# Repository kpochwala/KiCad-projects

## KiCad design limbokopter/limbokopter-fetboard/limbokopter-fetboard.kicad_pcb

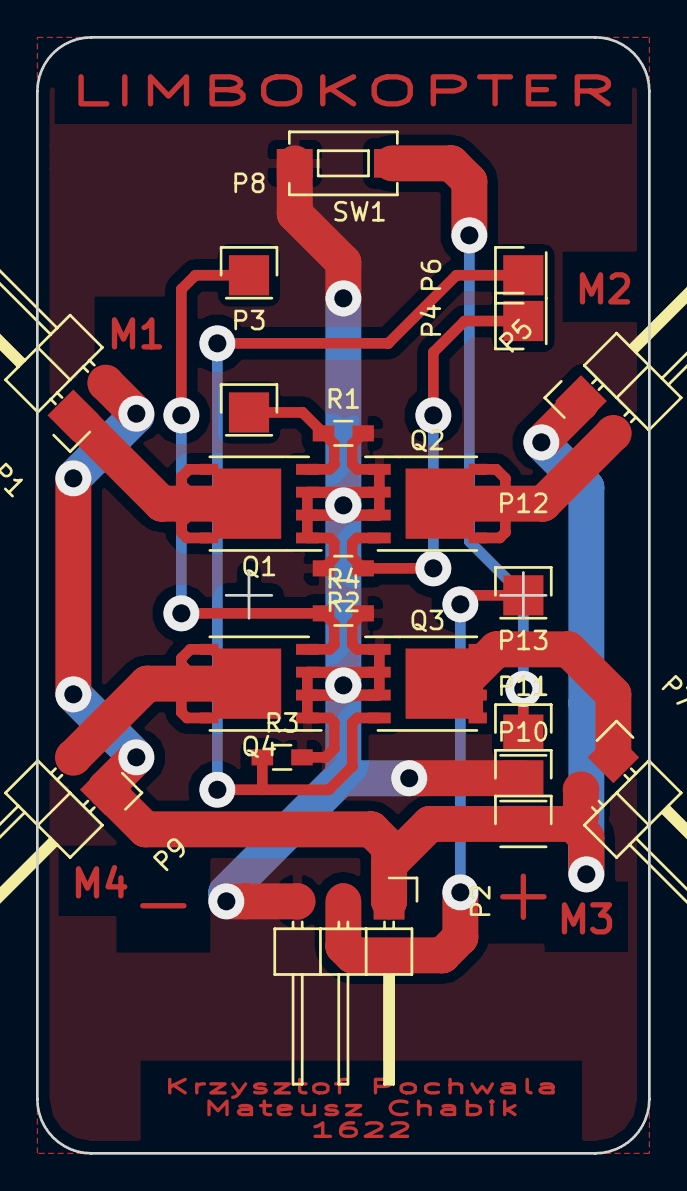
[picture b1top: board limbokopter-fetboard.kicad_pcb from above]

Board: 2 copper layers, 34.0 x 62.0 mm, 22 parts (0 on the bottom side), 12 nets.

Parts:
P1: M1; Pin_Header_Angled_1x02
P2: CONN_01X03; Pin_Header_Angled_1x03
P3: PWM1; Pin_Header_Straight_1x01
P4: PWM2; Pin_Header_Straight_1x01
P5: M2; Pin_Header_Angled_1x02
P6: PWM3; Pin_Header_Straight_1x01
P7: M3; Pin_Header_Angled_1x02
P8: PWM4; Pin_Header_Straight_1x01
P9: M4; Pin_Header_Angled_1x02
P10: RAW; Pin_Header_Straight_1x01
P11: GND; Pin_Header_Straight_1x01
P12: A2; Pin_Header_Straight_1x01
P13: RST; Pin_Header_Straight_1x01
Q1, Q2, Q3, Q4: 79N03; SO-8_PowerPAK_Vishay_Single
R1, R2, R3, R4: R; R_0603_HandSoldering
SW1: SW_PUSH; SW_SPST_EVQPE1

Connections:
+12V: P1.2, P2.1, P5.1, P7.2, P9.1, P10.1
GND: P2.3, P11.1, Q1.1, Q1.2, Q1.3, Q2.1, Q2.2, Q2.3, Q3.1, Q3.2, Q3.3, Q4.1, Q4.2, Q4.3, R1.2, R2.2, R3.2, R4.2, SW1.2
unnamed: P1.1, Q1.5
unnamed: P3.1, Q1.4, R1.1
unnamed: P4.1, Q2.4, R2.1
unnamed: P5.2, Q2.5
unnamed: P6.1, Q3.4, R3.1
unnamed: P7.1, Q3.5
unnamed: P8.1, Q4.4, R4.1
unnamed: P9.2, Q4.5
unnamed: P2.2, P12.1
unnamed: P13.1, SW1.1

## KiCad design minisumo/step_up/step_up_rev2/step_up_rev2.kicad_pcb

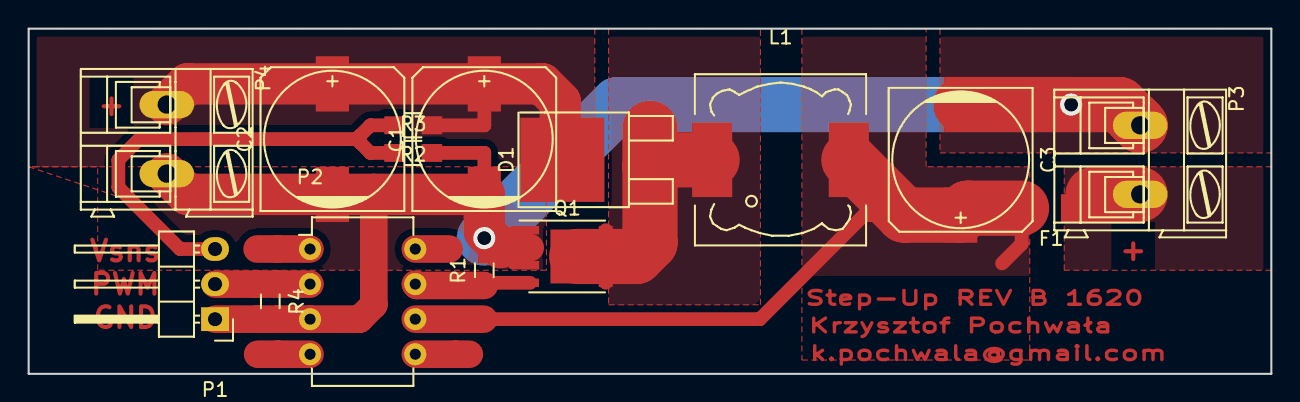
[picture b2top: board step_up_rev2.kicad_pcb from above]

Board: 2 copper layers, 90.0 x 25.0 mm, 15 parts (0 on the bottom side), 8 nets.

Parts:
C1, C2, C3: CP; c_elec_10x10
D1: D_Schottky_x2_KCom_AKA; TO-252-2Lead
F1: FUSE; Fuse_SMD1206_HandSoldering
L1: INDUCTOR; Choke_SMD_12x12mm_h8mm
P1: CONN_01X03; Pin_Header_Angled_1x03
P2: DIL8; DIP-8_W7.62mm
P3, P4: CONN_01X02; AK300-2
Q1: IRF7607PBF; SO-8_PowerPAK_Vishay_Single
R1, R4: R; R_0603_HandSoldering
R2, R3: R; R_0805_HandSoldering

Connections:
/Vin: C3.1, F1.2, L1.2, P2.6
/Vin_inductor: D1.1, D1.3, L1.1, Q1.5
/Vout: C1.1, C2.1, D1.2, P4.1, R2.1
GND: C1.2, C2.2, C3.2, P1.1, P2.3, P3.1, P4.2, Q1.1, Q1.2, Q1.3, R1.2, R3.2, R4.2
unnamed: F1.1, P3.2
unnamed: P1.2, P2.2, R4.1
unnamed: P1.3, R2.2, R3.1
unnamed: P2.7, Q1.4, R1.1

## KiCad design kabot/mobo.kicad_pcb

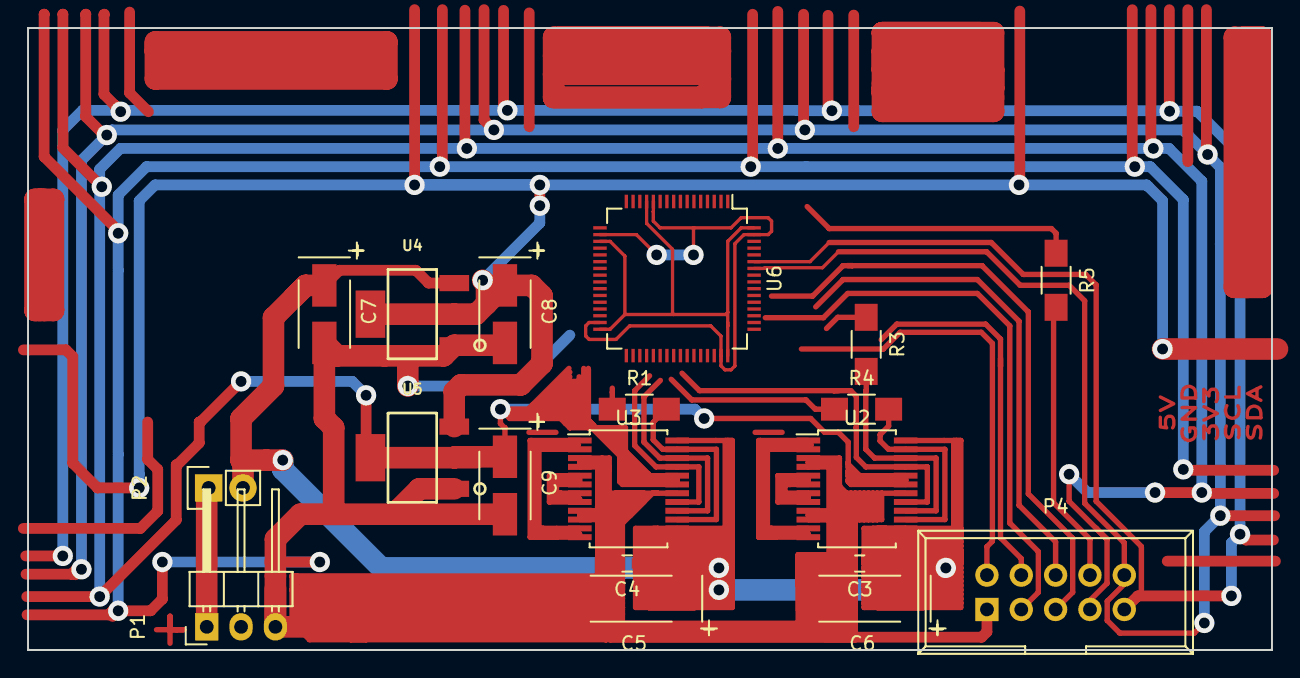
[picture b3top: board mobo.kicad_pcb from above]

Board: 2 copper layers, 92.0 x 46.0 mm, 19 parts (0 on the bottom side), 20 nets.

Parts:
C3, C4: 100n; C_0603_HandSoldering
C5, C6: 100u; TantalC_SizeC_EIA-6032_HandSoldering
C7, C8, C9: CP; TantalC_SizeB_EIA-3528_HandSoldering
P1: LIPO; Pin_Header_Angled_1x03
P2: SWITCH; Pin_Header_Straight_1x02
P4: CONN_02X05; IDC_Header_Straight_10pins
R1, R3, R4, R5: 0; R_1206_HandSoldering
U2, U3: TB6612
U4, U5: LM1117; LM1117_SOT223
U6: STM32F100R6Tx; LQFP-64_10x10mm_Pitch0.5mm

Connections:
+3V3: C9.1, P4.7, U2.19, U2.20, U3.19, U3.20, U5.2, U6.13, U6.19, U6.32, U6.48, U6.64
+5V: C8.1, U4.2, U5.1
+12V: C3.1, C4.1, C5.1, C6.1, C7.1, P2.2, U2.13, U2.14, U2.24, U3.13, U3.14, U3.24, U4.1
/RST: P4.8, R5.2
/mobo/M1A: U3.16, U3.22
/mobo/M1B: U3.17, U3.21
/mobo/M2B: U2.17, U2.21
/mobo/SCL: P4.10, U6.58
/mobo/SDA: P4.9, U6.59
/mobo/SWCLK: P4.4, U6.49
/mobo/SWDIO: P4.2, U6.46
/motors/M1PWM: R1.2, U3.15, U3.23
/motors/M2A: R3.2, U2.16, U2.22
/motors/M2PWM: R4.2, U2.15, U2.23
GND: C3.2, C4.2, C5.2, C6.2, C7.2, C8.2, C9.2, P1.3, P4.1, U2.3, U2.4, U2.9, U2.10, U2.18, U3.3, U3.4, U3.9, U3.10, U3.18, U4.3, U5.3, U6.12, U6.18, U6.31, U6.47, U6.63
unnamed: P1.1, P2.1
unnamed: U2.1, U2.2, U2.11, U2.12
unnamed: U2.5, U2.6, U2.7, U2.8
unnamed: U3.1, U3.2, U3.11, U3.12
unnamed: U3.5, U3.6, U3.7, U3.8

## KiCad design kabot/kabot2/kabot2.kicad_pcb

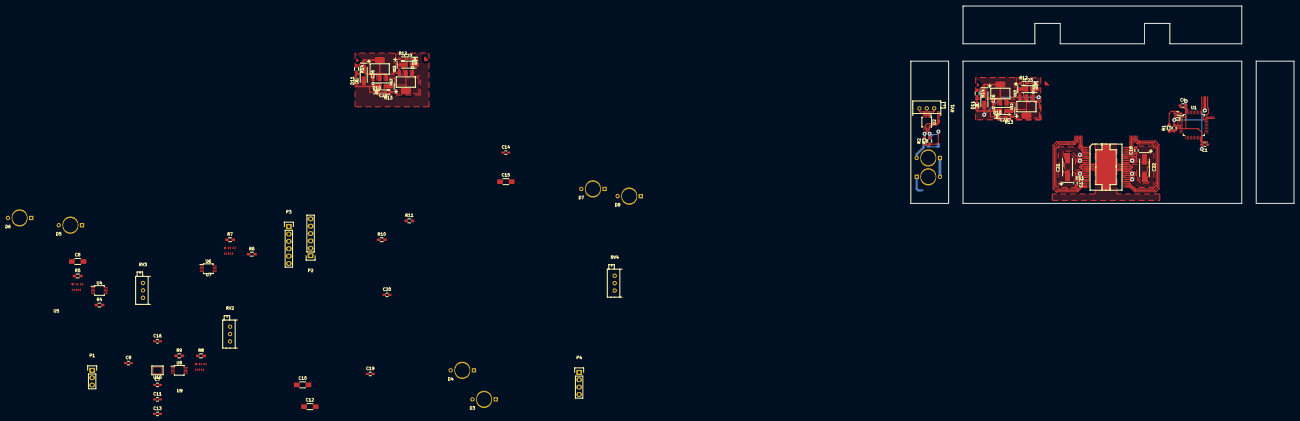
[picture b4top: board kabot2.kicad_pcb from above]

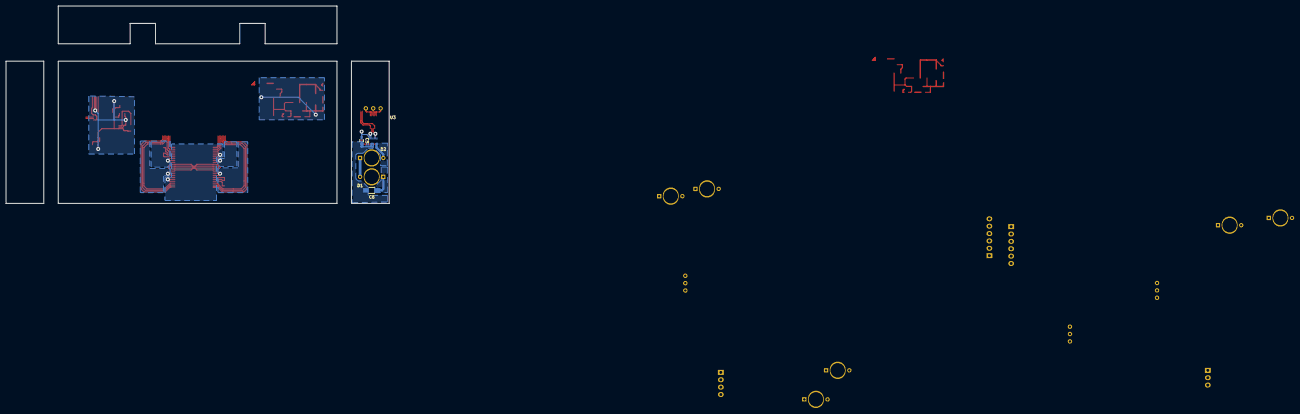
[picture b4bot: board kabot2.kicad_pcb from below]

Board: 2 copper layers, 132.0 x 68.0 mm, 82 parts (5 on the bottom side), 41 nets.

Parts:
C1, C2, C3, C4, C5, C7, C9, C11, C13, C14, C17, C18, C19, C20: 100nF; C_0603_HandSoldering
C6, C8, C10, C12: 1uF; C_1206_HandSoldering
C15: 10uF; C_1206_HandSoldering
C16: 10nF; C_0603_HandSoldering
C21, C22: 100uF; TantalC_SizeC_EIA-6032_HandSoldering
C23, C23#2, C24, C24#2, C26, C26#2: 10uF; TantalC_SizeA_EIA-3216_HandSoldering
D1, D2, D3, D4, D5, D6, D7, D8: TSHF6210; TSHF6210_Reverse
D9, D9#2: R; LED_0603
D10, D10#2: G; LED_0603
D11, D11#2: B; LED_0603
P1: CONN_01X03; Pin_Header_Straight_1x03
P2, P3: IE2-512; Pin_Header_Straight_1x06
P4: SWD; Pin_Header_Straight_1x04
R1, R2, R3, R4, R5, R6, R7, R8, R9: 4k7; R_0603_HandSoldering
R10, R11: 220R; R_0603_HandSoldering
R12, R12#2, R13, R13#2, R14, R14#2: 1K; R_0603_HandSoldering
RV1, RV2, RV3, RV4: POT; Potentiometer_Bourns_3296X_3-8Zoll_Inline_ScrewFront
U1: STM32F030C6Tx; LQFP-48_7x7mm_Pitch0.5mm
U2, U4, U6, U8: LTC4316; MSOP-10_3x3mm_Pitch0.5mm
U3, U5, U7, U9: VCNL3020; VCNL3020_footprint
U10: LSM330TR; LGA24
U11: MC33932; HSOP_44
U12, U12#2: LM1117-5; LM1117_SOT223
U13, U13#2: LM1117-3.3; LM1117_SOT223

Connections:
+3V3: C1.1, C2.1, C3.1, C4.1, C5.1, C7.1, C9.1, C11.1, C13.1, C14.1, C15.1, C26.1, C26#2.1, R1.1, R2.1, R3.1, R4.1, R5.1, R6.1, R7.1, R8.1, R9.1, R14.1, R14#2.1, RV1.1, RV2.1, RV3.1, RV4.1, U1.1, U1.9, U1.24, U1.48, U2.4, U2.5, U3.5, U4.4, U4.5, U5.5, U6.4, U6.5, U7.5, U8.4, U8.5, U9.5, U10.1, U10.3, U10.5, U10.6, U10.7, U10.8, U10.22, U10.23, U10.24, U11.3, U11.25, U13.2, U13#2.2
+5V: C6.1, C8.1, C10.1, C12.1, C24.1, C24#2.1, D1.1, D3.1, D5.1, D7.1, P2.4, P3.4, R13.1, R13#2.1, U12.2, U12#2.2, U13.1, U13#2.1
+12V: C17.1, C18.1, C19.1, C20.1, C21.1, C22.1, C23.1, C23#2.1, R12.1, R12#2.1, U11.4, U11.5, U11.6, U11.17, U11.18, U11.26, U11.27, U11.28, U11.39, U11.40, U12.1, U12#2.1
/CONNECTORS/AMOT+: P2.1, U11.14, U11.15, U11.16
/CONNECTORS/AMOT-: P2.2, U11.29, U11.30, U11.31
/CONNECTORS/SWCLK: P4.2, U1.37
/CONNECTORS/SWDIO: P4.1, U1.34
/MCU/ACURRENT: R10.1, U11.2
/MCU/BCURRENT: R11.1, U11.24
/MCU/RST: R1.2, U1.7
/MOTOR-DRIVER/AMOT1: P3.1, U11.7, U11.8, U11.9
/MOTOR-DRIVER/AMOT2: P3.2, U11.36, U11.37, U11.38
/SCL: U1.35, U2.10, U4.10, U6.10, U8.10, U10.4
/SDA: U1.36, U2.7, U6.7, U8.7, U10.2
GND: C1.2, C2.2, C3.2, C4.2, C5.2, C6.2, C7.2, C8.2, C9.2, C10.2, C11.2, C12.2, C13.2, C14.2, C15.2, C16.2, C19.2, C20.2, C21.2, C22.2, C23.2, C23#2.2, C24.2, C24#2.2, C26.2, C26#2.2, D9.1, D9#2.1, D10.1, D10#2.1, D11.1, D11#2.1, P1.3, P2.3, P3.3, P4.4, R10.2, R11.2, RV1.3, RV2.3, RV3.3, RV4.3, U1.8, U1.23, U1.47, U2.1, U2.2, U3.7, U4.1, U4.2, U5.7, U6.1, U6.2, U7.7, U8.1, U8.2, U9.7, U10.14, U10.15, U10.16, U10.17, U10.18, U10.19, U10.20, U11.10, U11.11, U11.12, U11.13, U11.32, U11.33, U11.34, U11.35, U11.49, U12.3, U12#2.3, U13.3, U13#2.3
unnamed: C16.1, U10.21
unnamed: C17.2, U11.19
unnamed: C18.2, U11.41
unnamed: D1.2, D2.1
unnamed: D2.2, U3.8
unnamed: D3.2, D4.1
unnamed: D4.2, U5.8
unnamed: D5.2, D6.1
unnamed: D6.2, U7.8
unnamed: D7.2, D8.1
unnamed: D8.2, U9.8
unnamed: D9.2, D9#2.2, R12.2, R12#2.2
unnamed: D10.2, D10#2.2, R13.2, R13#2.2
unnamed: D11.2, D11#2.2, R14.2, R14#2.2
unnamed: R2.2, U2.8, U3.2
unnamed: R3.2, U2.9, U3.4
unnamed: R4.2, U4.8, U5.2
unnamed: R5.2, U4.9, U5.4
unnamed: R6.2, U6.8, U7.2
unnamed: R7.2, U6.9, U7.4
unnamed: R8.2, U8.8, U9.2
unnamed: R9.2, U8.9, U9.4
unnamed: RV1.2, U2.3
unnamed: RV2.2, U4.3
unnamed: RV3.2, U6.3
unnamed: RV4.2, U8.3

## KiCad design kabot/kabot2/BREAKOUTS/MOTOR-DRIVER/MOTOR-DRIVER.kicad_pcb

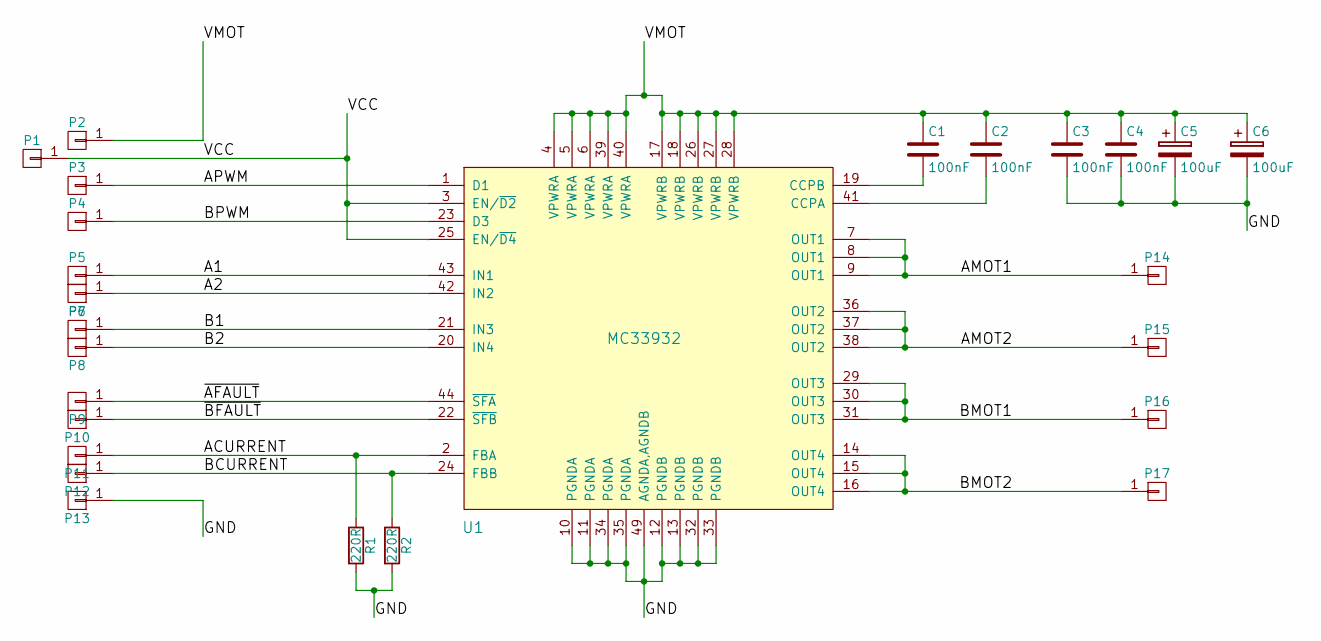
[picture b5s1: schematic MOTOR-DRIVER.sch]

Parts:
C1, C2, C3, C4: 100nF; C_0603_HandSoldering
C5, C6: 100uF; TantalC_SizeC_EIA-6032_HandSoldering
P1, P2, P3, P4, P5, P6, P7, P8, P9, P10, P11, P12, P13, P14, P15, P16, P17: CONN_01X01; Pin_Header_Straight_1x01
R1, R2: 220R; R_0805_HandSoldering
U1: MC33932; HSOP_44

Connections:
/A1: P5.1, U1.43 (IN1)
/A2: P6.1, U1.42 (IN2)
/ACURRENT: P11.1, R1.1, U1.2 (FBA)
/AMOT1: P14.1, U1.7 (OUT1), U1.8 (OUT1), U1.9 (OUT1)
/AMOT2: P15.1, U1.36 (OUT2), U1.37 (OUT2), U1.38 (OUT2)
/APWM: P3.1, U1.1 (D1)
/B1: P7.1, U1.21 (IN3)
/B2: P8.1, U1.20 (IN4)
/BCURRENT: P12.1, R2.1, U1.24 (FBB)
/BMOT1: P16.1, U1.29 (OUT3), U1.30 (OUT3), U1.31 (OUT3)
/BMOT2: P17.1, U1.14 (OUT4), U1.15 (OUT4), U1.16 (OUT4)
/BPWM: P4.1, U1.23 (D3)
/GND: C3.2, C4.2, C5.2, C6.2, P13.1, R1.2, R2.2, U1.10 (PGNDA), U1.11 (PGNDA), U1.12 (PGNDB), U1.13 (PGNDB), U1.32 (PGNDB), U1.33 (PGNDB), U1.34 (PGNDA), U1.35 (PGNDA), U1.49 (AGNDA,AGNDB)
/VCC: P1.1, U1.3 (EN/~D2), U1.25 (EN/~D4)
/VMOT: C1.1, C2.1, C3.1, C4.1, C5.1, C6.1, P2.1, U1.4 (VPWRA), U1.5 (VPWRA), U1.6 (VPWRA), U1.17 (VPWRB), U1.18 (VPWRB), U1.26 (VPWRB), U1.27 (VPWRB), U1.28 (VPWRB), U1.39 (VPWRA), U1.40 (VPWRA)
/~AFAULT: P9.1, U1.44 (~SFA)
/~BFAULT: P10.1, U1.22 (~SFB)
unnamed: C1.2, U1.19 (CCPB)
unnamed: C2.2, U1.41 (CCPA)

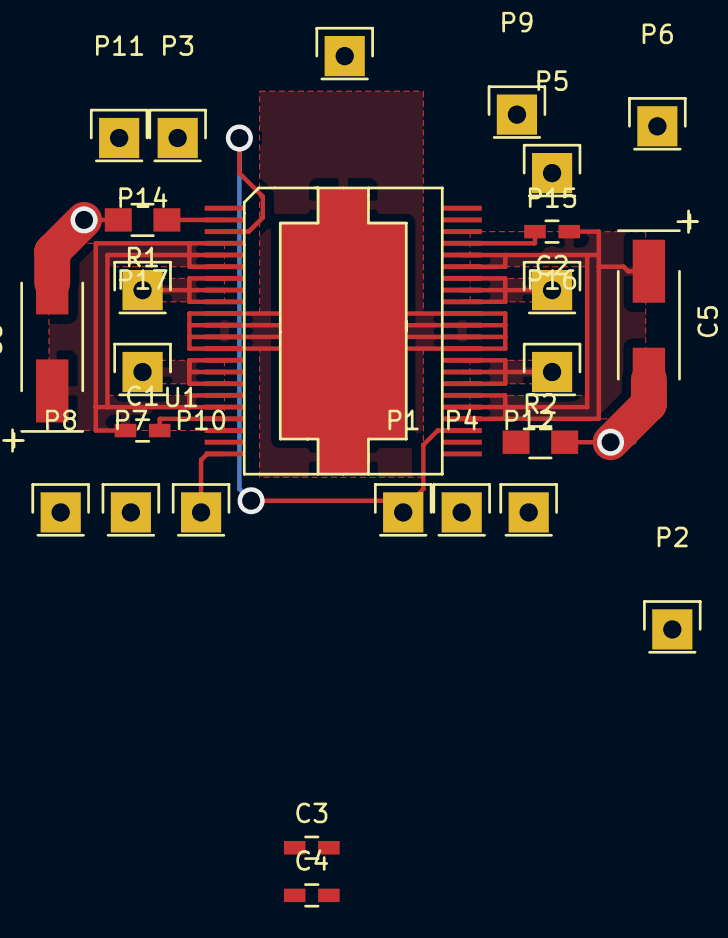
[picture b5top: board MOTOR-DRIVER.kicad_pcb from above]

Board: 2 copper layers, 26 parts (0 on the bottom side), 19 nets.

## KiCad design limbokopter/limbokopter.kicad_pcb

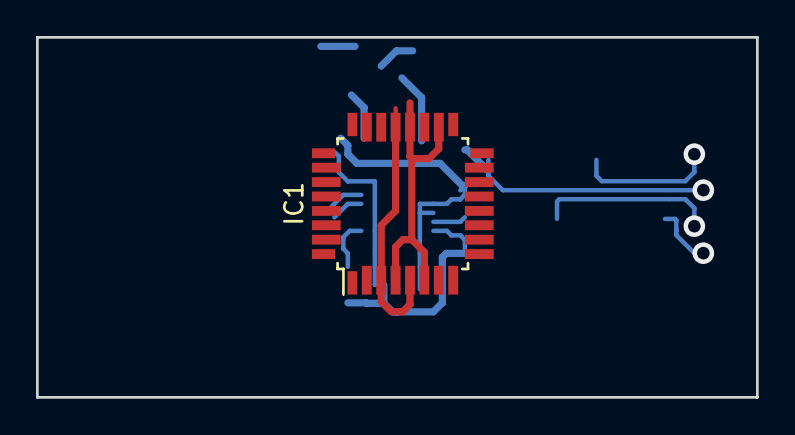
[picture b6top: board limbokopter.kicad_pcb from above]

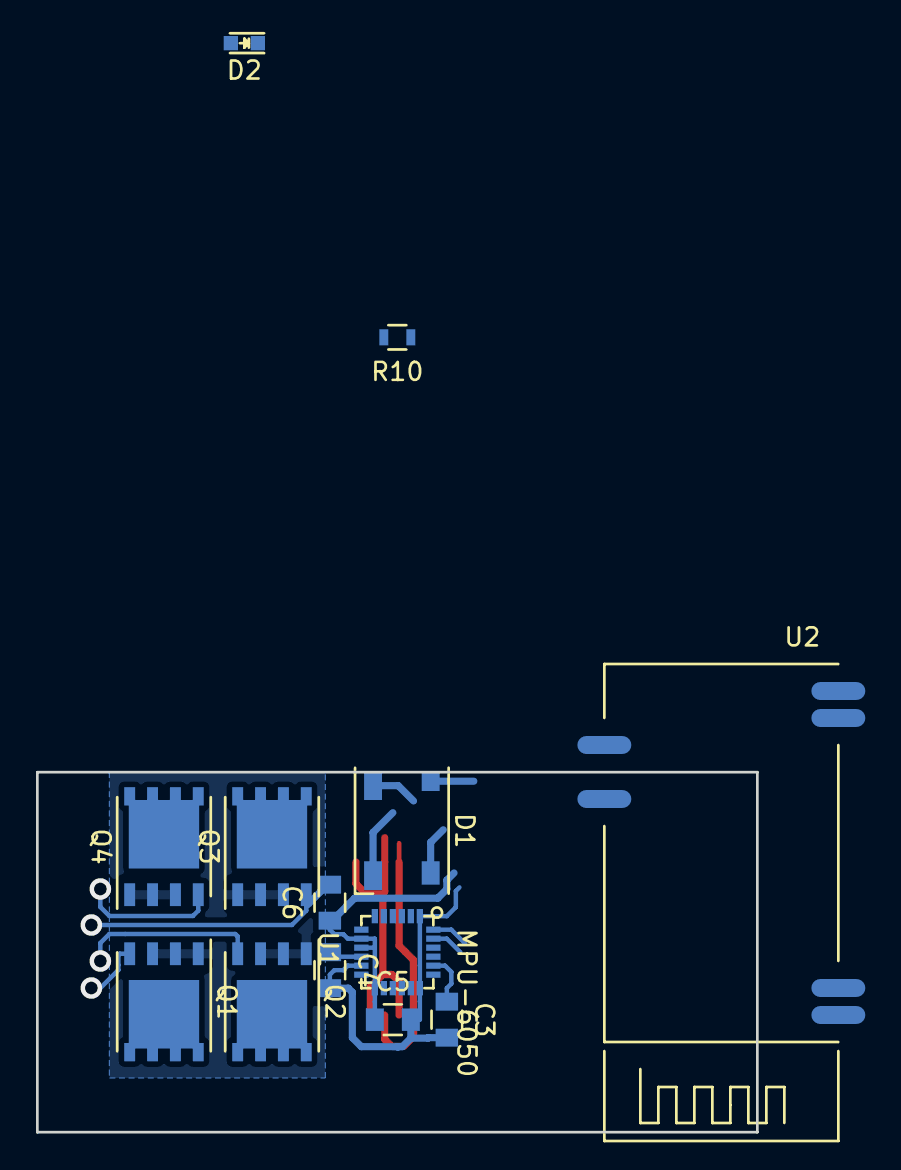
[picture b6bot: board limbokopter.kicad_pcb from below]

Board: 2 copper layers, 40.0 x 20.0 mm, 14 parts (13 on the bottom side), 18 nets.

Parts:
C3: 2n2; C_0805
C4, C6: 0u1; C_0805
C5: 10n; C_0805
D1: Led_RGB_CA; LED_WS2812B-PLCC4
D2: LED; LED_0603
IC1: ATMEGA328-A; TQFP-32_7x7mm_Pitch0.8mm
Q1, Q2, Q3, Q4: IRF7607PBF; SO-8_PowerPAK_Vishay_Single
R10: R; R_0603
U1: MPU-6050
U2: HC06; HC06-minimal

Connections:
+3V3: C5.1, C6.1, IC1.4, IC1.6, IC1.18, IC1.20, U1.8, U1.9, U1.13, U2.12
/Bluetooth/RXD: IC1.31, U2.2
/IMU/SCL: IC1.28, U1.23
/IMU/SDA: IC1.27, U1.24
/Microcontroller/8_LED: D1.3, IC1.12
/Microcontroller/11_PWM_LEDA: D1.1, IC1.15
/Microcontroller/12_LED: D1.2, IC1.16
/Microcontroller/13_LED: D1.4, IC1.17
/Microcontroller/RXD: IC1.30, U2.1
/motor/M1: IC1.9, Q1.4
/motor/M2: IC1.10, Q2.4
/motor/M3: IC1.13, Q3.4
/motor/M4: IC1.14, Q4.4
GND: C3.2, C4.2, C5.2, C6.2, IC1.3, IC1.5, IC1.21, Q1.1, Q1.2, Q1.3, Q2.1, Q2.2, Q2.3, Q3.1, Q3.2, Q3.3, Q4.1, Q4.2, Q4.3, R10.2, U1.1, U1.11, U1.18, U2.13, U2.26
unnamed: C3.1, U1.20
unnamed: C4.1, U1.10
unnamed: D2.1, R10.1
unnamed: D2.2, U2.24

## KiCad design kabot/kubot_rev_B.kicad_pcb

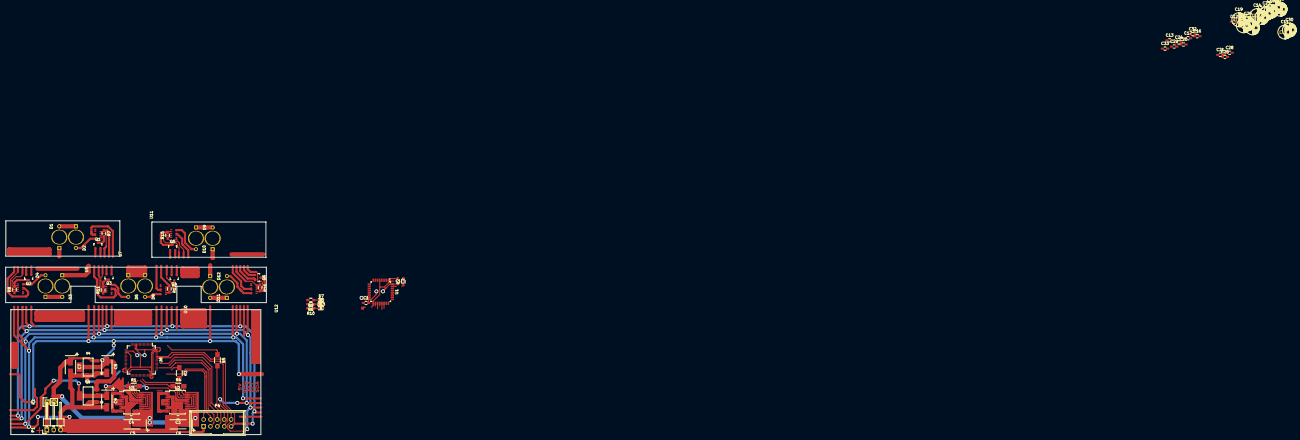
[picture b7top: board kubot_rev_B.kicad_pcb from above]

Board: 2 copper layers, 96.0 x 78.7 mm, 81 parts (0 on the bottom side), 53 nets.

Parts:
C1, C2, C3, C4, C12, C13, C16, C17, C20, C21, C24, C25, C28, C29, C32, C33: 100n; C_0603_HandSoldering
C5, C6: 100u; TantalC_SizeC_EIA-6032_HandSoldering
C7, C8, C9: CP; TantalC_SizeB_EIA-3528_HandSoldering
C10, C11, C18, C19, C26, C27: 10u; C_Radial_D5_L6_P2.5
C14, C15, C22, C23, C30, C31: 22u; C_Radial_D5_L6_P2.5
D1, D2, D3, D4, D6, D8, D9, D10, D11, D12: TSHF6210; TSHF6210_Reverse
D5, D7, D13: LED; LED_0603
P1: LIPO; Pin_Header_Angled_1x03
P2: SWITCH; Pin_Header_Straight_1x02
P4: CONN_02X05; IDC_Header_Straight_10pins
Q1, Q2, Q3, Q4, Q5, Q6: BSS138; SOT-23
R1, R3, R4, R5: 0; R_1206_HandSoldering
R2, R7, R8, R11, R12, R15, R16: 4K7; R_0603_HandSoldering
R6, R9, R10: R; R_0603_HandSoldering
U1: STM32F030K6Tx; LQFP-32_7x7mm_Pitch0.8mm
U2, U3: TB6612
U4, U5: LM1117; LM1117_SOT223
U6: STM32F100R6Tx; LQFP-64_10x10mm_Pitch0.5mm
U7, U8, U9, U10, U11, U12: VCNL3020; VCNL3020_footprint

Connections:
+3V3: C1.1, C2.1, C9.1, C10.1, C11.1, C12.1, C13.1, C18.1, C19.1, C20.1, C21.1, C26.1, C27.1, C28.1, C29.1, D5.2, D7.2, D13.2, P4.7, R7.1, R8.1, R11.1, R12.1, R15.1, R16.1, U1.1, U1.5, U1.17, U2.19, U2.20, U3.19, U3.20, U5.2, U6.13, U6.19, U6.32, U6.48, U6.64, U7.5, U8.5, U9.5, U10.5, U11.5, U12.5
+5V: C8.1, C14.1, C15.1, C16.1, C17.1, C22.1, C23.1, C24.1, C25.1, C30.1, C31.1, C32.1, C33.1, D1.1, D3.1, D6.1, D8.1, D9.1, D11.1, U4.2, U5.1
+12V: C3.1, C4.1, C5.1, C6.1, C7.1, P2.2, U2.13, U2.14, U2.24, U3.13, U3.14, U3.24, U4.1
/RST: P4.8, R5.2
/VCNL/SCL: U7.4, U8.4, U9.4, U10.4, U11.4, U12.4
/VCNL/SDA: Q1.2, Q2.2, Q3.2, Q4.2, Q5.2, Q6.2
/mobo/M1A: U1.20, U3.16, U3.22
/mobo/M1B: U1.19, U3.17, U3.21
/mobo/M1PWM: R1.1, U1.18
/mobo/M2A: R3.1, U1.25
/mobo/M2B: U1.22, U2.17, U2.21
/mobo/M2PWM: R4.1, U1.21
/mobo/MISO: P4.6, U1.27
/mobo/MOSI: P4.5, U1.28
/mobo/RST: R5.1, U1.4
/mobo/SCK: P4.3, U1.26
/mobo/SCL: P4.10, U6.58
/mobo/SDA: P4.9, U6.59
/mobo/SWCLK: P4.4, U6.49
/mobo/SWDIO: P4.2, U6.46
/motors/M1PWM: R1.2, U3.15, U3.23
/motors/M2A: R3.2, U2.16, U2.22
/motors/M2PWM: R4.2, U2.15, U2.23
GND: C1.2, C2.2, C3.2, C4.2, C5.2, C6.2, C7.2, C8.2, C9.2, C10.2, C11.2, C12.2, C13.2, C14.2, C15.2, C16.2, C17.2, C18.2, C19.2, C20.2, C21.2, C22.2, C23.2, C24.2, C25.2, C26.2, C27.2, C28.2, C29.2, C30.2, C31.2, C32.2, C33.2, P1.3, P4.1, R2.2, U2.3, U2.4, U2.9, U2.10, U2.18, U3.3, U3.4, U3.9, U3.10, U3.18, U4.3, U5.3, U6.12, U6.18, U6.31, U6.47, U6.63, U7.7, U8.7, U9.7, U10.7, U11.7, U12.7
unnamed: D1.2, D2.1
unnamed: D2.2, U7.8
unnamed: D3.2, D4.1
unnamed: D4.2, U8.8
unnamed: D5.1, R6.1
unnamed: D6.2, U9.8
unnamed: D7.1, R9.1
unnamed: D8.2, U10.8
unnamed: D9.2, D10.1
unnamed: D10.2, U11.8
unnamed: D11.2, D12.1
unnamed: D12.2, U12.8
unnamed: D13.1, R10.1
unnamed: P1.1, P2.1
unnamed: Q1.3, R7.2, U7.2
unnamed: Q2.3, R8.2, U8.2
unnamed: Q3.3, R11.2, U9.2
unnamed: Q4.3, R12.2, U10.2
unnamed: Q5.3, R15.2, U11.2
unnamed: Q6.3, R16.2, U12.2
unnamed: R2.1, U1.31
unnamed: R6.2, U1.11
unnamed: R9.2, U1.12
unnamed: R10.2, U1.10
unnamed: U1.16, U1.32
unnamed: U2.1, U2.2, U2.11, U2.12
unnamed: U2.5, U2.6, U2.7, U2.8
unnamed: U3.1, U3.2, U3.11, U3.12
unnamed: U3.5, U3.6, U3.7, U3.8

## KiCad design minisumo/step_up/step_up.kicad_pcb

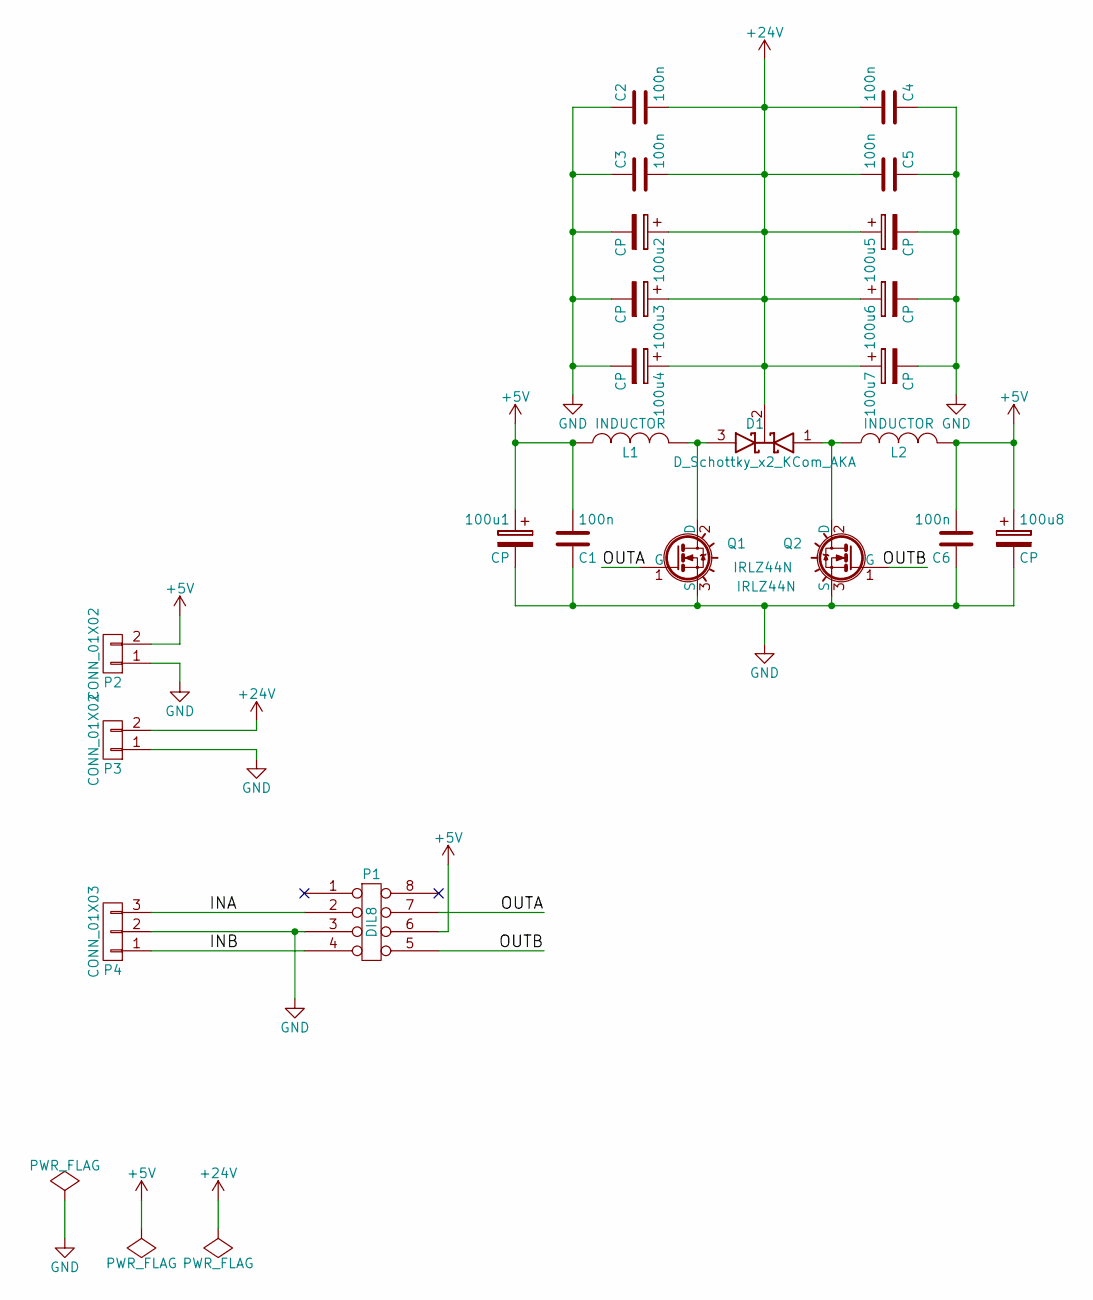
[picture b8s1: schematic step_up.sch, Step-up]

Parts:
100u1, 100u2, 100u3, 100u4, 100u5, 100u6, 100u7, 100u8: CP; TantalC_SizeC_EIA-6032_HandSoldering
C1, C2, C3, C4, C5, C6: 100n; C_0603_HandSoldering
D1: D_Schottky_x2_KCom_AKA; TO-220_Neutral123_Vertical_LargePads
L1, L2: INDUCTOR; Choke_SMD_12x12mm_h8mm
P1: DIL8; SOIC-8_3.9x4.9mm_Pitch1.27mm
P2, P3: CONN_01X02; AK300-2
P4: CONN_01X03; Pin_Header_Angled_1x03
Q1, Q2: IRLZ44N; TO-220_Neutral123_Vertical_LargePads

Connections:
+5V: 100u1.1, 100u8.1, C1.2, C6.2, L1.1, L2.2, P1.6, P2.2
+24V: 100u2.1, 100u3.1, 100u4.1, 100u5.1, 100u6.1, 100u7.1, C2.2, C3.2, C4.2, C5.2, D1.2 (K), P3.2
/INA: P1.2, P4.3
/INB: P1.4, P4.1
/OUTA: P1.7, Q1.1 (G)
/OUTB: P1.5, Q2.1 (G)
GND: 100u1.2, 100u2.2, 100u3.2, 100u4.2, 100u5.2, 100u6.2, 100u7.2, 100u8.2, C1.1, C2.1, C3.1, C4.1, C5.1, C6.1, P1.3, P2.1, P3.1, P4.2, Q1.3 (S), Q2.3 (S)
unnamed: D1.1 (A), L2.1, Q2.2 (D)
unnamed: D1.3 (A), L1.2, Q1.2 (D)

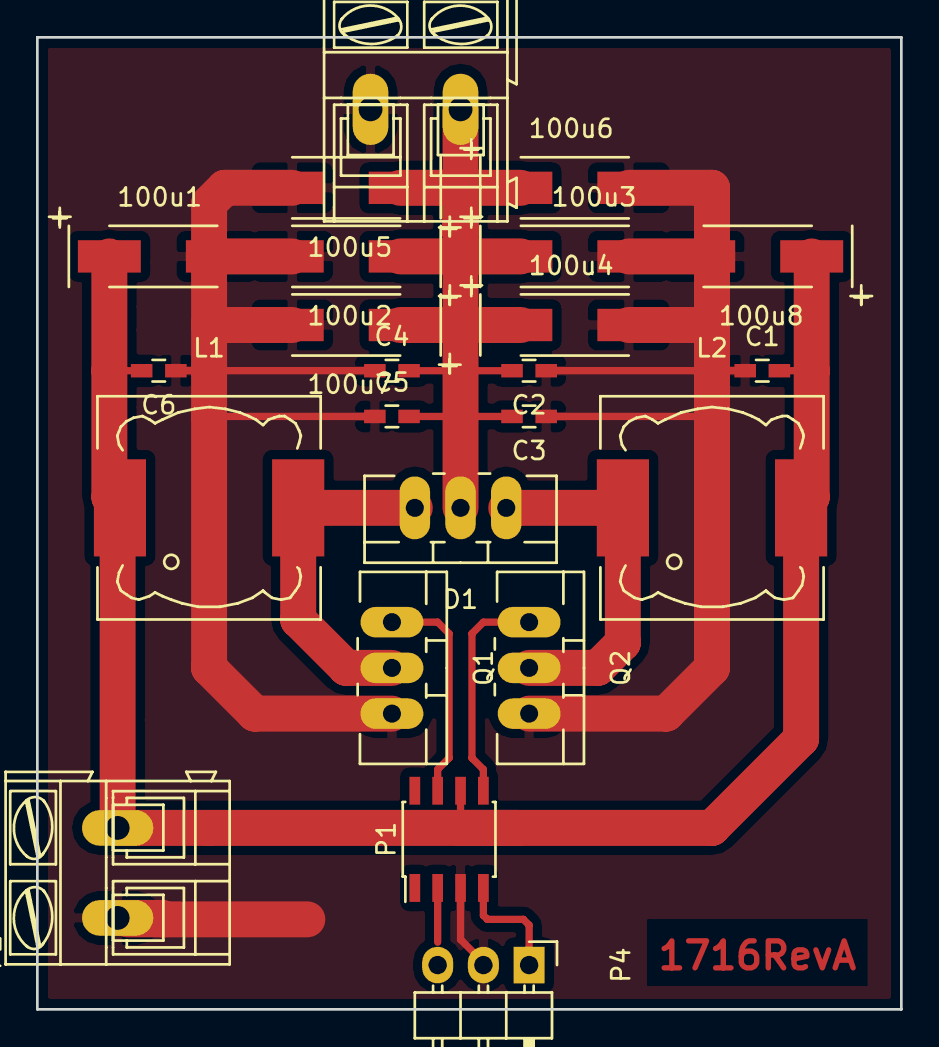
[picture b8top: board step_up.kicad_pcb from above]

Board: 2 copper layers, 48.0 x 54.0 mm, 23 parts (0 on the bottom side), 9 nets.

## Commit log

2016-09-22 Inital commit
